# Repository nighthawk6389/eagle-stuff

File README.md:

# eagle-stuff
Stuff I made for PCB in Eagle

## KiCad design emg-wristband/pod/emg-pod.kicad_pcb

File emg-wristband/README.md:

# EMG wristband: main pod, rev A

KiCad project for the main pod: two ADS1298 converters, a Seeed XIAO nRF52840 Sense, a 3.0 V analog rail
with a USB interlock, and a vibration-motor driver. The brief is in `CLAUDE.md`. What is still
uncertain is in `OPEN.md`; read that before trusting anything here.

Status (2026-11-28): schematic drawn and ERC clean; board laid out and routed, 49 x 49 mm with a notch
under the antenna, four layers; reviewed once and reworked; fabrication files written, for the single
board and for the board in a 74 x 74 mm assembly frame; reviewed a second time, with findings still
open (`OPEN.md`, "Second review"). Nothing has been ordered or built. The layout's open points are under
"Layout" in `OPEN.md`.

## Where things are

| Path | What |
|---|---|
| `out/emg-pod-schematic.pdf` | The schematic for review, five pages |
| `out/bom-jlcpcb.csv` | Bill of materials from the schematic, JLCPCB columns, one LCSC number per line |
| `out/stock-check.md` | Stock and assembly type of every BOM line, with the date it was read |
| `out/erc.rpt` | KiCad's ERC report |
| `out/fab/` | The single board: Gerbers and drill files (also zipped), `cpl-jlcpcb.csv` (placement) and the BOM |
| `out/fab-panel/` | The same board in its 74 x 74 mm assembly frame: **the files for a JLCPCB Standard-assembly order** |
| `out/drc.rpt`, `out/drc-panel.rpt` | KiCad's DRC reports for the routed board and for the frame |
| `out/board-top.png`, `out/board-bottom.png`, `out/panel-top.png` | KiCad's rendering of the bare board, both sides, and of the frame |
| `pod/` | The KiCad 9 project (`emg-pod.kicad_pro`, schematic and `emg-pod.kicad_pcb`) and the frame (`emg-pod-panel.kicad_pcb`). Opens in KiCad 9 or newer |
| `pod/lib/` | Every symbol the schematic uses, and Seeed's XIAO footprint (plus a copy without the two NFC pads) |
| `gen/` | The Python that writes the schematic and the board |
| `tools/` | JLCPCB stock lookup |
| `docs/sources.md` | The datasheets and Seeed files each pin table came from |

## The schematic is generated

`gen/build.py` writes the `.kicad_sch` files. **Edits made in KiCad's schematic editor are lost the
next time it runs.** Either keep changing the generator, or stop using it and edit in KiCad from then on.

    python3 gen/build.py           # needs KiCad 9's kicad-cli on the path
    python3 tools/stock_report.py  # re-reads stock from jlcpcb.com

`build.py` does four things: writes the sheets, runs ERC, exports KiCad's netlist and compares all 552
pins with the tables in `gen/design.py` (which take their pin numbers from `gen/parts.py`, copied from
the datasheets), and exports the PDF and BOM. It exits non-zero if ERC or the comparison fails.

- `gen/parts.py`: pin tables and LCSC numbers. Each table names its datasheet.
- `gen/design.py`: which pin goes to which net, and where each part is drawn. The board is built from
  the same tables, so schematic and board cannot disagree about a net.
- `gen/kisch.py`, `gen/sexp.py`: KiCad file writing.

## The board is generated too

Five steps, each a script. **Edits made in KiCad's board editor are lost when they run again**, same
as for the schematic.

    /usr/bin/python3 gen/board.py                      # placement, rules, fixed routes -> pod/emg-pod-unrouted.kicad_pcb
    /usr/bin/python3 gen/route.py freerouting-2.1.0.jar   # autoroute the rest (Freerouting, about 9 minutes)
    /usr/bin/python3 gen/finish.py                     # leftovers, ground pours, plane vias, silkscreen -> pod/emg-pod.kicad_pcb
    /usr/bin/python3 gen/fab.py                        # Gerbers, drill, placement file -> out/fab/
    /usr/bin/python3 gen/panel.py                      # the board in its assembly frame -> pod/emg-pod-panel.kicad_pcb, out/fab-panel/

They need the `pcbnew` Python module that comes with KiCad 9 (the system Python on Ubuntu) and, for
`route.py`, Java and the Freerouting 2.1.0 jar from github.com/freerouting/freerouting (not in this repo).

- `gen/board.py` holds everything that was decided by hand: the outline, the design rules, where each
  part sits, and the routes that must not be left to an autorouter. Those are the 32 electrode lines
  (connector, resistor array, converter pin, in one straight line on the top layer), their fan-out on
  the back to the filter capacitors and to the ESD arrays, the via to a plane for every supply and
  ground pin of the converters, VCAP1, a ground via beside every ground pad, and lanes on the back for
  the seven nets that cross from the XIAO to the left half below the notch (five signals, the battery
  and VBUS; a lane the routers end up not using is removed again). The outline, with its
  notch under the XIAO's antenna, and the keep-outs under the module's bare pads are there too. It also names the
  areas reserved for the input lines (`quiet_zones`): the fan-out on the back around each converter
  and the stubs under it on the front. The routers lay nothing there.
- `gen/route.py` hands the rest to Freerouting. Ground is left out of that: ground pads are joined by
  the plane, the pours on both outer layers and the vias `finish.py` adds.
- `gen/finish.py` completes what Freerouting gave up on with a small grid router (`gen/lastmile.py`),
  pours ground on the outer layers, gives supply pads a via to their plane, stitches the pours to the
  ground plane, removes dead-end stubs, and runs KiCad's DRC. It prints what is still open, if anything.
- `gen/fab.py` writes the Gerbers, drill files and placement file, checks every pad's net against
  `gen/design.py`, checks that no routed track entered a reserved area and that the planes are
  filled between the vias of each row, reports how close other signals come to an input line and
  how close vias come to pads, and writes the full DRC report. It exits non-zero unless DRC has no
  errors, nothing is unconnected, the reserved areas are clean and the planes have no gaps.

- `gen/panel.py` copies the finished board into a 74 x 74 mm frame (JLCPCB's smallest size for
  Standard assembly is 70 x 70): a routed slot around the board, five tabs with a row of small holes each,
  three fiducials and four tooling holes on the rails. It does not move the board or refill its
  zones, checks that all copper is the same as in the single board, and runs DRC on the result.
  Run it again whenever `pod/emg-pod.kicad_pcb` changes. How to order and what is unverified:
  `OPEN.md`.

Any change to `gen/board.py` moves many of the autorouted tracks on the next run. The board in `pod/`
is the result of one run, and `out/fab/` and `out/fab-panel/` were made from exactly that file.

Layers: 1 signal and parts, 2 ground (one plane, no splits), 3 supplies (DVDD above y = 26.0 mm, AVDD
below, ground
fill elsewhere), 4 signal. No parts on the back; five bare pads are there, under the XIAO (SWD, ground and 3.3 V for a probe).

## Sheets

1. Overview: rails and the XIAO pin map.
2. Power: battery connector, LP5907 3.0 V analog rail, the USB interlock, the motor driver.
3. MCU: the XIAO and its test points, including SWD.
4. Converter A: strip connector, ESD arrays, input network, ADS1298, bypass, bias drive, clock master.
5. Converter B: the same block, clocked from A, bias amplifier unused.

Converter A parts are numbered 100-199 and converter B parts 200-299, so each block stays
recognisable when the pod is split later.

## Choices made while drawing (details in OPEN.md)

- **XIAO Sense on Standard assembly** (owner's decision). JLCPCB marks the Sense "Standard Only"; every
  other part is cleared for Economic. Standard assembly wants boards of at least 70 x 70 mm with rails and fiducials, hence the frame.
- **47k in every skin-facing line**, so any path through the wearer crosses 94k.
- **Digital supply always on, analog supply gated.** The interlock only switches the 3.0 V rail.
- **Interlock:** a MOSFET holds the regulator's enable low whenever the XIAO's 5V pin (USB VBUS) is up.
- **SPI clock and data-in on D5 and D4**, the only XIAO pins Nordic rates for fast signals.
- **Motor on two wire pads**, with a series resistor sized for a 3 V coin motor on a 4.2 V cell.
- **Tantalum on VCAP1**, because the datasheet warns about ceramics there on boards that vibrate.

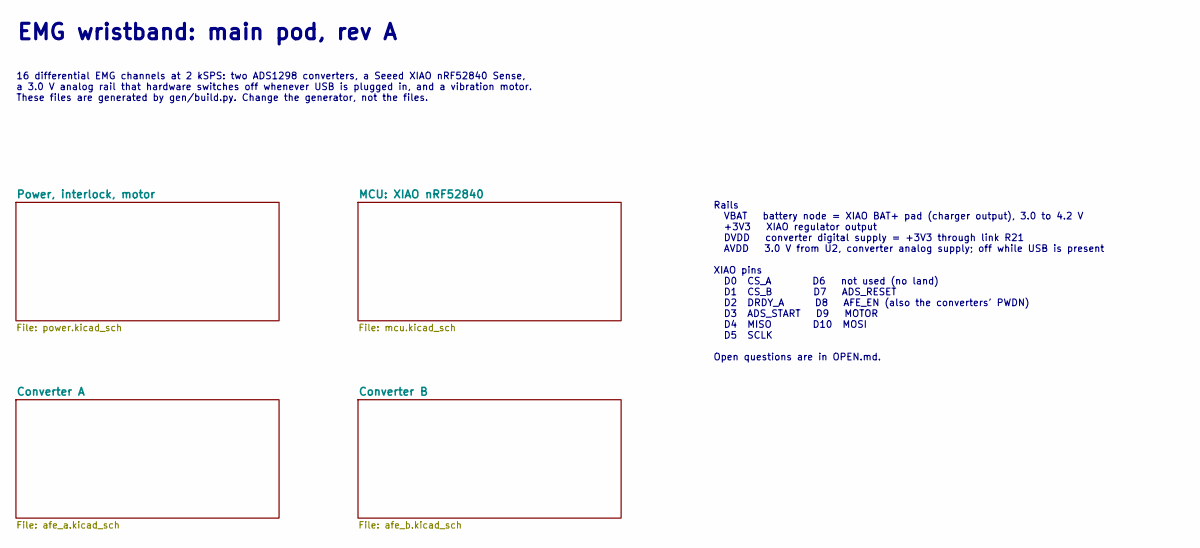
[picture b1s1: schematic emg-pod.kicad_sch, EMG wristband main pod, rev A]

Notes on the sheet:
EMG wristband: main pod, rev A
16 differential EMG channels at 2 kSPS: two ADS1298 converters, a Seeed XIAO nRF52840 Sense, a 3.0 V analog rail that hardware switches off whenever USB is plugged in, and a vibration motor. These files are generated by gen/build.py. Change the generator, not the files.
Rails VBAT battery node = XIAO BAT+ pad (charger output), 3.0 to 4.2 V +3V3 XIAO regulator output DVDD converter digital supply = +3V3 through link R21 AVDD 3.0 V from U2, converter analog supply; off while USB is present XIAO pins D0 CS_A D6 not used (no land) D1 CS_B D7 ADS_RESET D2 DRDY_A D8 AFE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

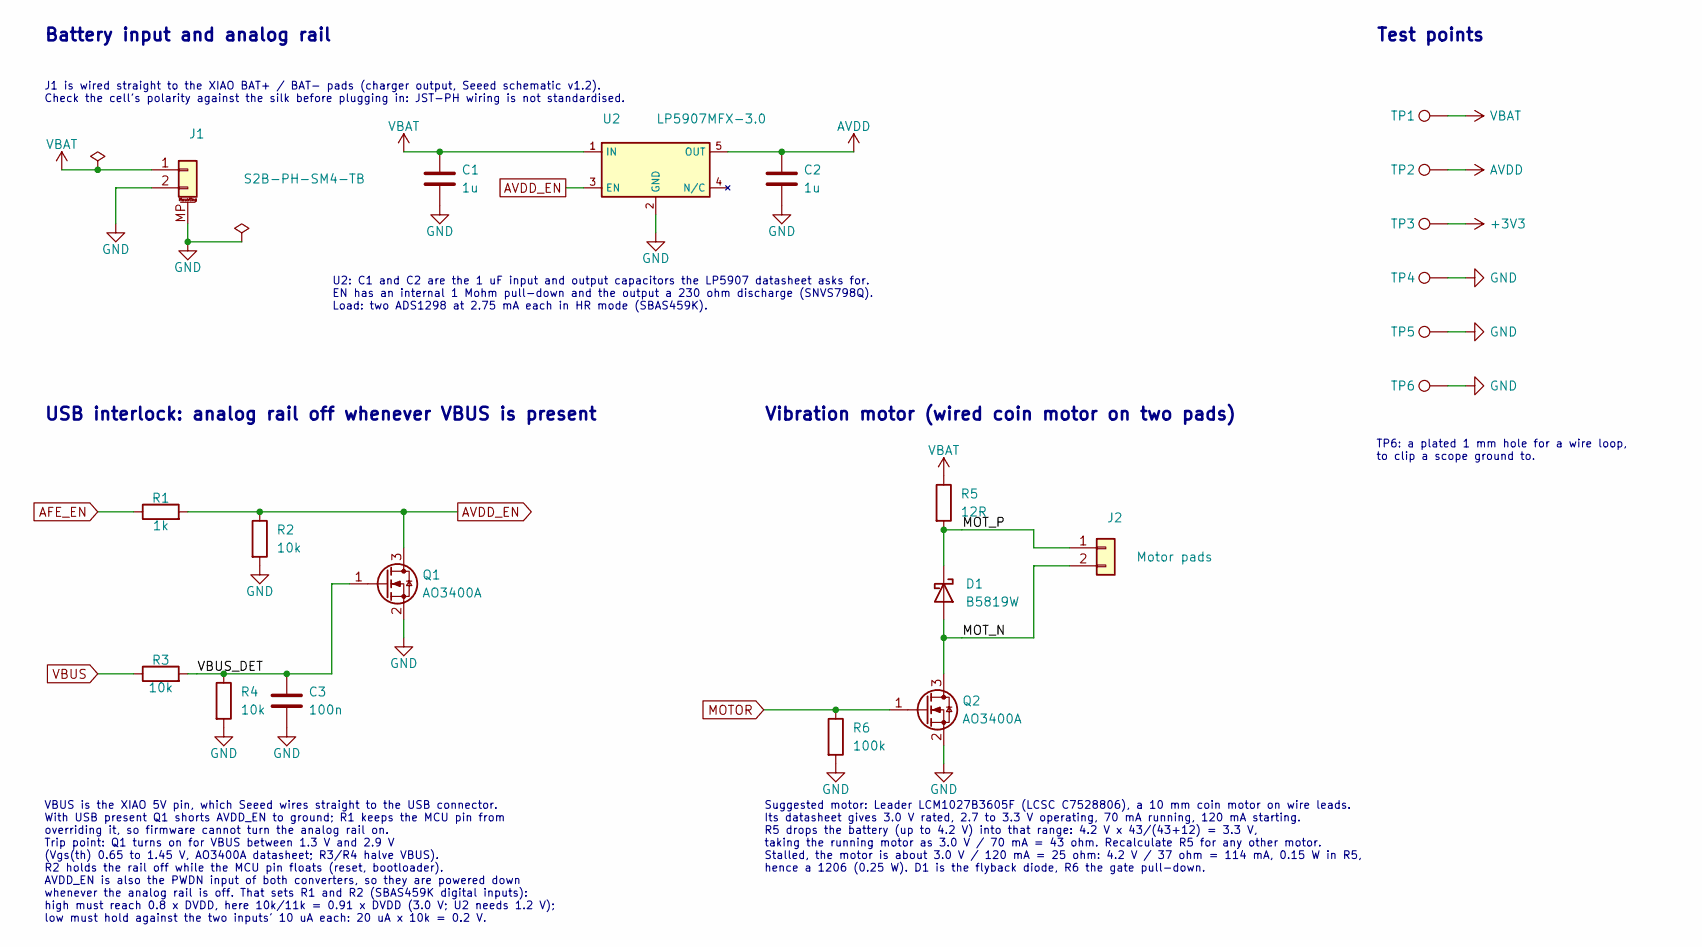
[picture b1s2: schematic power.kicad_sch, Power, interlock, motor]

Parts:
C1, C2: 1u; C_0402_1005Metric; MPN CL05A105KA5NQNC; LCSC C52923
C3: 100n; C_0402_1005Metric; MPN CL05B104KO5NNNC; LCSC C1525
D1: B5819W; D_SOD-123; MPN B5819W SL; LCSC C8598
J1: S2B-PH-SM4-TB; JST_PH_S2B-PH-SM4-TB_1x02-1MP_P2.00mm_Horizontal; MPN S2B-PH-SM4-TB(LF)(SN); LCSC C295747
J2: Motor pads; SolderWire-0.127sqmm_1x02_P3.7mm_D0.48mm_OD1mm
Q1, Q2: AO3400A; SOT-23; MPN AO3400A; LCSC C20917
R1: 1k; R_0402_1005Metric; MPN 0402WGF1001TCE; LCSC C11702
R2, R3, R4: 10k; R_0402_1005Metric; MPN 0402WGF1002TCE; LCSC C25744
R5: 12R; R_1206_3216Metric; MPN 1206W4F120JT5E; LCSC C17913
R6: 100k; R_0402_1005Metric; MPN 0402WGF1003TCE; LCSC C25741
TP1, TP2, TP3, TP4, TP5: TestPoint; TestPoint_Pad_D1.0mm_bare
TP6: TestPoint; TestPoint_THTPad_D2.0mm_Drill1.0mm
U2: LP5907MFX-3.0; SOT-23-5; MPN LP5907MFX-3.0/NOPB; LCSC C475492

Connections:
+3V3: TP3.1; also elsewhere on the board
AFE_EN: R1.1; also elsewhere on the board
AVDD: C2.1, TP2.1, U2.5 (OUT); also elsewhere on the board
AVDD_EN: Q1.3 (D), R1.2, R2.1, U2.3 (EN); also elsewhere on the board
GND: C1.2, C2.2, C3.2, J1.2, J1.MP (MountPin), Q1.2 (S), Q2.2 (S), R2.2, R4.2, R6.2, TP4.1, TP5.1, TP6.1, U2.2 (GND); also elsewhere on the board
MOTOR: Q2.1 (G), R6.1; also elsewhere on the board
MOT_N: D1.2 (A), J2.2, Q2.3 (D)
MOT_P: D1.1 (K), J2.1, R5.2
VBAT: C1.1, J1.1, R5.1, TP1.1, U2.1 (IN); also elsewhere on the board
VBUS: R3.1; also elsewhere on the board
VBUS_DET: C3.1, Q1.1 (G), R3.2, R4.1

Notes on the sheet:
Battery input and analog rail
J1 is wired straight to the XIAO BAT+ / BAT- pads (charger output, Seeed schematic v1.2). Check the cell's polarity against the silk before plugging in: JST-PH wiring is not standardised.
U2: C1 and C2 are the 1 uF input and output capacitors the LP5907 datasheet asks for. EN has an internal 1 Mohm pull-down and the output a 230 ohm discharge (SNVS798Q). Load: two ADS1298 at 2.75 mA each in HR mode (SBAS459K).
USB interlock: analog rail off whenever VBUS is present
VBUS is the XIAO 5V pin, which Seeed wires straight to the USB connector. With USB present Q1 shorts AVDD_EN to ground; R1 keeps the MCU pin from overriding it, so firmware cannot turn the analog rail on. Trip point: Q1 turns on for VBUS between 1.3 V and 2.9 V (Vgs(th) 0.65 to 1.45 V, AO3400A data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
Vibration motor (wired coin motor on two pads)
Suggested motor: Leader LCM1027B3605F (LCSC C7528806), a 10 mm coin motor on wire leads. Its datasheet gives 3.0 V rated, 2.7 to 3.3 V operating, 70 mA running, 120 mA starting. R5 drops the battery (up to 4.2 V) into that range: 4.2 V x 43/(43+12) = 3.3 V, taking the running motor as 3.0 V / 70 mA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
Test points
TP6: a plated 1 mm hole for a wire loop, to clip a scope ground to.

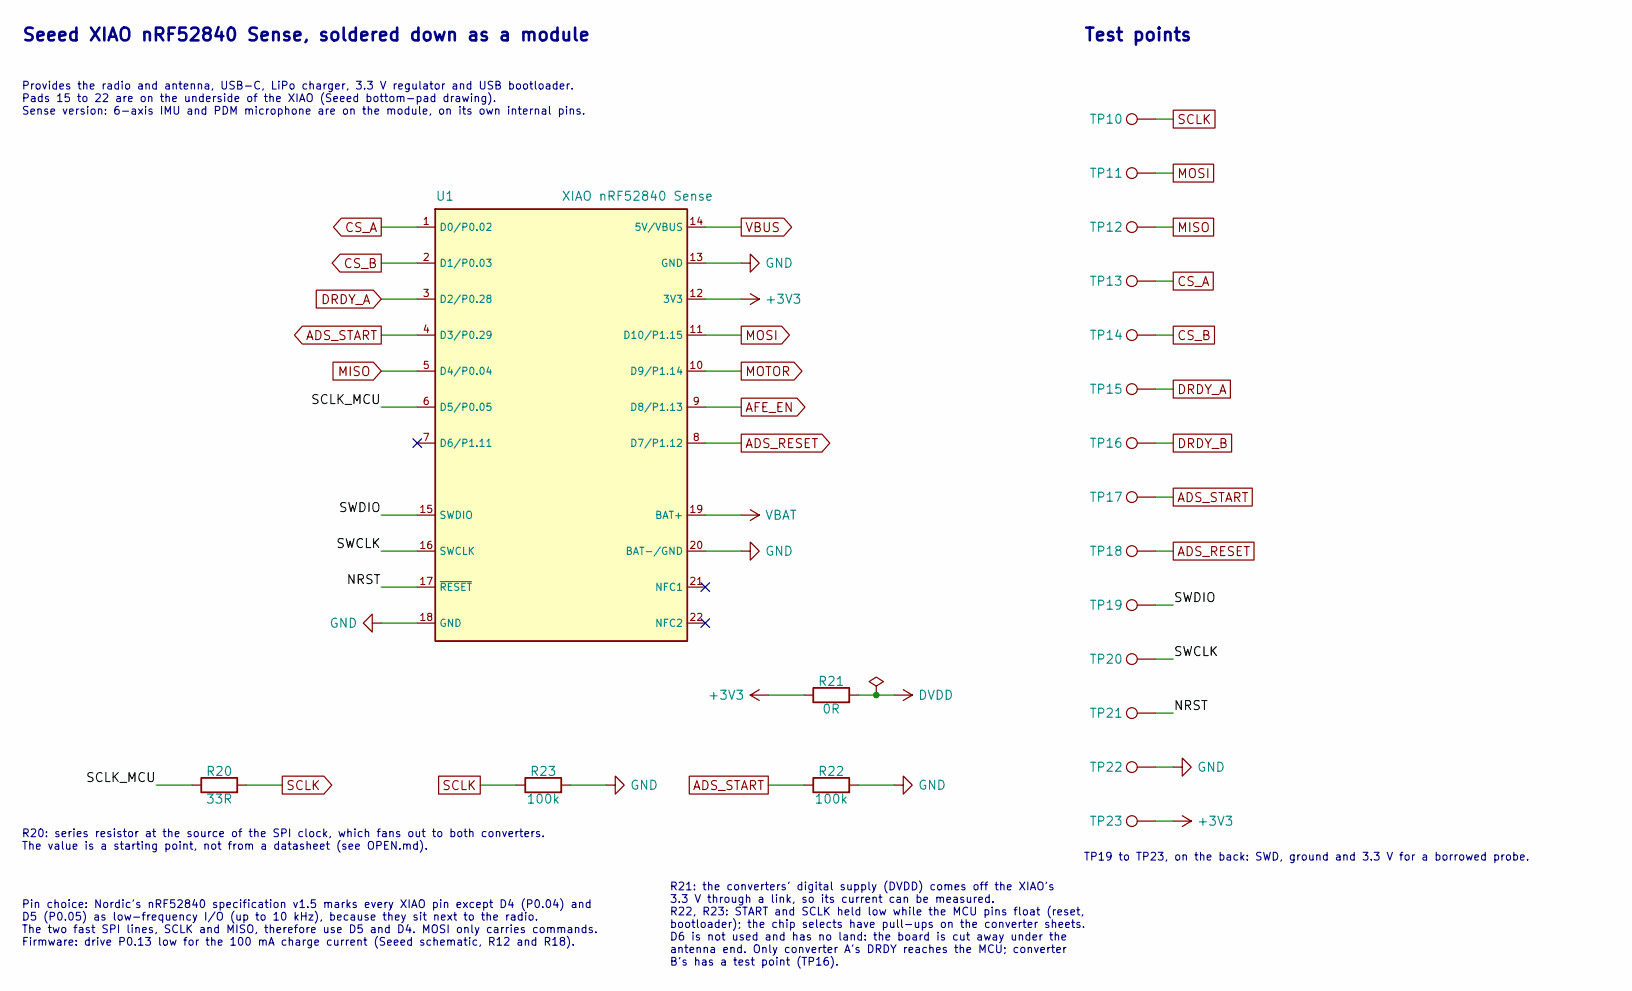
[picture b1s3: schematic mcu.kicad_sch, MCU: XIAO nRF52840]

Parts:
R20: 33R; R_0402_1005Metric; MPN 0402WGF330JTCE; LCSC C25105
R21: 0R; R_0402_1005Metric; MPN 0402WGF0000TCE; LCSC C17168
R22, R23: 100k; R_0402_1005Metric; MPN 0402WGF1003TCE; LCSC C25741
TP10, TP11, TP12, TP13, TP14, TP15, TP16, TP17, TP18, TP19, TP20, TP21, TP22, TP23: TestPoint; TestPoint_Pad_D1.0mm_bare
U1: XIAO nRF52840 Sense; XIAO-nRF52840-SMD-pod; MPN Seeed 102010469; LCSC C17401557

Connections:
+3V3: R21.1, TP23.1, U1.12 (3V3); also elsewhere on the board
ADS_RESET: TP18.1, U1.8 (D7/P1.12); also elsewhere on the board
ADS_START: R22.1, TP17.1, U1.4 (D3/P0.29); also elsewhere on the board
AFE_EN: U1.9 (D8/P1.13); also elsewhere on the board
CS_A: TP13.1, U1.1 (D0/P0.02); also elsewhere on the board
CS_B: TP14.1, U1.2 (D1/P0.03); also elsewhere on the board
DRDY_A: TP15.1, U1.3 (D2/P0.28); also elsewhere on the board
DRDY_B: TP16.1; also elsewhere on the board
DVDD: R21.2; also elsewhere on the board
GND: R22.2, R23.2, TP22.1, U1.13 (GND), U1.18 (GND), U1.20 (BAT-/GND); also elsewhere on the board
MISO: TP12.1, U1.5 (D4/P0.04); also elsewhere on the board
MOSI: TP11.1, U1.11 (D10/P1.15); also elsewhere on the board
MOTOR: U1.10 (D9/P1.14); also elsewhere on the board
NRST: TP21.1, U1.17 (~RESET)
SCLK: R20.2, R23.1, TP10.1; also elsewhere on the board
SCLK_MCU: R20.1, U1.6 (D5/P0.05)
SWCLK: TP20.1, U1.16 (SWCLK)
SWDIO: TP19.1, U1.15 (SWDIO)
VBAT: U1.19 (BAT+); also elsewhere on the board
VBUS: U1.14 (5V/VBUS); also elsewhere on the board

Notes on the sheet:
Seeed XIAO nRF52840 Sense, soldered down as a module
Provides the radio and antenna, USB-C, LiPo charger, 3.3 V regulator and USB bootloader. Pads 15 to 22 are on the underside of the XIAO (Seeed bottom-pad drawing). Sense version: 6-axis IMU and PDM microphone are on the module, on its own internal pins.
R20: series resistor at the source of the SPI clock, which fans out to both converters. The value is a starting point, not from a datasheet (see OPEN.md).
R21: the converters' digital supply (DVDD) comes off the XIAO's 3.3 V through a link, so its current can be measured. R22, R23: START and SCLK held low while the MCU pins float (reset, bootloader); the chip selects have pull-ups on the converter sheets. D6 is not used and has no land: the board is 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
Pin choice: Nordic's nRF52840 specification v1.5 marks every XIAO pin except D4 (P0.04) and D5 (P0.05) as low-frequency I/O (up to 10 kHz), because they sit next to the radio. The two fast SPI lines, SCLK and MISO, therefore use D5 and D4. MOSI only carries commands. Firmware: drive P0.13 low for t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
Test points
TP19 to TP23, on the back: SWD, ground and 3.3 V for a borrowed probe.

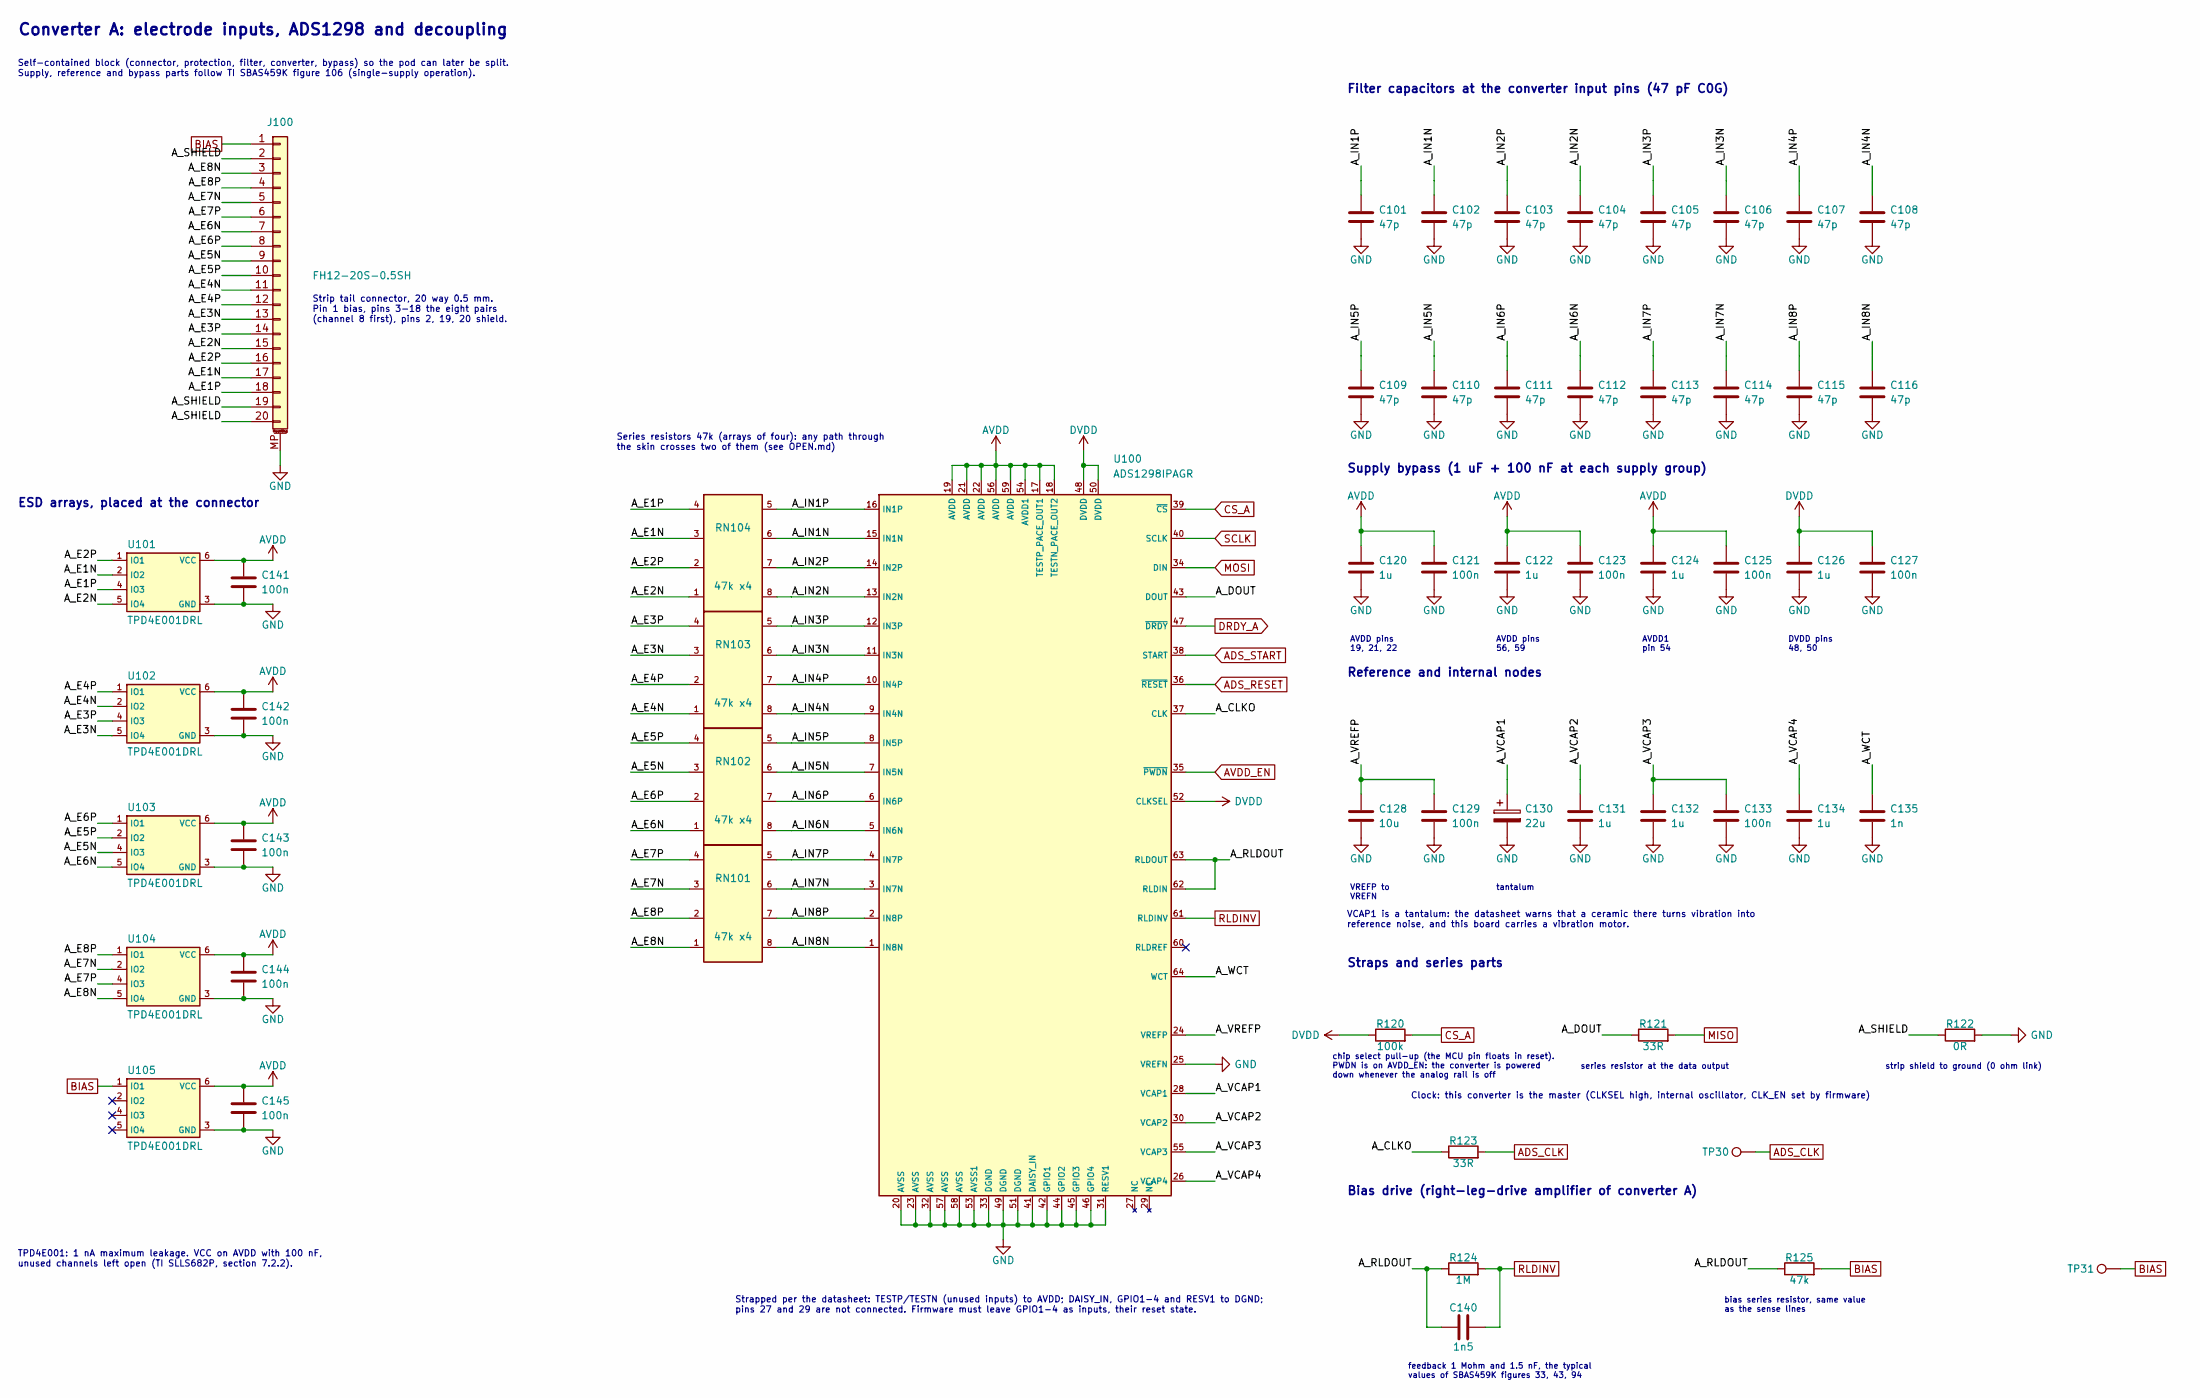
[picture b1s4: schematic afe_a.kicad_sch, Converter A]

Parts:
C101, C102, C103, C104, C105, C106, C107, C108, C109, C110, C111, C112, C113, C114, C115, C116: 47p; C_0402_1005Metric; MPN 0402CG470J500NT; LCSC C1567
C120, C122, C124, C126, C131, C132, C134: 1u; C_0402_1005Metric; MPN CL05A105KA5NQNC; LCSC C52923
C121, C123, C125, C127, C129, C133, C141, C142, C143, C144, C145: 100n; C_0402_1005Metric; MPN CL05B104KO5NNNC; LCSC C1525
C128: 10u; C_0603_1608Metric; MPN CL10A106KP8NNNC; LCSC C19702
C130: 22u; CP_EIA-3528-21_Kemet-B; MPN T491B226M010AT; LCSC C117031
C135: 1n; C_0402_1005Metric; MPN 0402B102K500NT; LCSC C1523
C140: 1n5; C_0603_1608Metric; MPN 0603B152K500NT; LCSC C1595
J100: FH12-20S-0.5SH; Hirose_FH12-20S-0.5SH_1x20-1MP_P0.50mm_Horizontal; MPN FH12-20S-0.5SH(55); LCSC C596730
R120: 100k; R_0402_1005Metric; MPN 0402WGF1003TCE; LCSC C25741
R121, R123: 33R; R_0402_1005Metric; MPN 0402WGF330JTCE; LCSC C25105
R122: 0R; R_0402_1005Metric; MPN 0402WGF0000TCE; LCSC C17168
R124: 1M; R_0402_1005Metric; MPN 0402WGF1004TCE; LCSC C26083
R125: 47k; R_0402_1005Metric; MPN 0402WGF4702TCE; LCSC C25792
RN101, RN102, RN103, RN104: 47k x4; R_Array_Convex_4x0402; MPN 4D02WGJ0473TCE; LCSC C2028
TP30, TP31: TestPoint; TestPoint_Pad_D1.0mm_bare
U100: ADS1298IPAGR; TQFP-64_10x10mm_P0.5mm; MPN ADS1298IPAGR; LCSC C527440
U101, U102, U103, U104, U105: TPD4E001DRL; SOT-563; MPN TPD4E001DRLR; LCSC C527516

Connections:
ADS_CLK: R123.2, TP30.1; also elsewhere on the board
ADS_RESET: U100.36 (~RESET); also elsewhere on the board
ADS_START: U100.38 (START); also elsewhere on the board
AVDD: C120.1, C121.1, C122.1, C123.1, C124.1, C125.1, C141.1, C142.1, C143.1, C144.1, C145.1, U100.17 (TESTP_PACE_OUT1), U100.18 (TESTN_PACE_OUT2), U100.19 (AVDD), U100.21 (AVDD), U100.22 (AVDD), U100.54 (AVDD1), U100.56 (AVDD), U100.59 (AVDD), U101.6 (VCC), U102.6 (VCC), U103.6 (VCC), U104.6 (VCC), U105.6 (VCC); also elsewhere on the board
AVDD_EN: U100.35 (~PWDN); also elsewhere on the board
A_CLKO: R123.1, U100.37 (CLK)
A_DOUT: R121.1, U100.43 (DOUT)
A_E1N: J100.17, RN104.3, U101.2 (IO2)
A_E1P: J100.18, RN104.4, U101.4 (IO3)
A_E2N: J100.15, RN104.1, U101.5 (IO4)
A_E2P: J100.16, RN104.2, U101.1 (IO1)
A_E3N: J100.13, RN103.3, U102.5 (IO4)
A_E3P: J100.14, RN103.4, U102.4 (IO3)
A_E4N: J100.11, RN103.1, U102.2 (IO2)
A_E4P: J100.12, RN103.2, U102.1 (IO1)
A_E5N: J100.9, RN102.3, U103.4 (IO3)
A_E5P: J100.10, RN102.4, U103.2 (IO2)
A_E6N: J100.7, RN102.1, U103.5 (IO4)
A_E6P: J100.8, RN102.2, U103.1 (IO1)
A_E7N: J100.5, RN101.3, U104.2 (IO2)
A_E7P: J100.6, RN101.4, U104.4 (IO3)
A_E8N: J100.3, RN101.1, U104.5 (IO4)
A_E8P: J100.4, RN101.2, U104.1 (IO1)
A_IN1N: C102.1, RN104.6, U100.15 (IN1N)
A_IN1P: C101.1, RN104.5, U100.16 (IN1P)
A_IN2N: C104.1, RN104.8, U100.13 (IN2N)
A_IN2P: C103.1, RN104.7, U100.14 (IN2P)
A_IN3N: C106.1, RN103.6, U100.11 (IN3N)
A_IN3P: C105.1, RN103.5, U100.12 (IN3P)
A_IN4N: C108.1, RN103.8, U100.9 (IN4N)
A_IN4P: C107.1, RN103.7, U100.10 (IN4P)
A_IN5N: C110.1, RN102.6, U100.7 (IN5N)
A_IN5P: C109.1, RN102.5, U100.8 (IN5P)
A_IN6N: C112.1, RN102.8, U100.5 (IN6N)
A_IN6P: C111.1, RN102.7, U100.6 (IN6P)
A_IN7N: C114.1, RN101.6, U100.3 (IN7N)
A_IN7P: C113.1, RN101.5, U100.4 (IN7P)
A_IN8N: C116.1, RN101.8, U100.1 (IN8N)
A_IN8P: C115.1, RN101.7, U100.2 (IN8P)
A_RLDOUT: C140.1, R124.1, R125.1, U100.62 (RLDIN), U100.63 (RLDOUT)
A_SHIELD: J100.2, J100.19, J100.20, R122.1
A_VCAP1: C130.1, U100.28 (VCAP1)
A_VCAP2: C131.1, U100.30 (VCAP2)
A_VCAP3: C132.1, C133.1, U100.55 (VCAP3)
A_VCAP4: C134.1, U100.26 (VCAP4)
A_VREFP: C128.1, C129.1, U100.24 (VREFP)
A_WCT: C135.1, U100.64 (WCT)
BIAS: J100.1, R125.2, TP31.1, U105.1 (IO1); also elsewhere on the board
CS_A: R120.2, U100.39 (~CS); also elsewhere on the board
DRDY_A: U100.47 (~DRDY); also elsewhere on the board
DVDD: C126.1, C127.1, R120.1, U100.48 (DVDD), U100.50 (DVDD), U100.52 (CLKSEL); also elsewhere on the board
GND: C101.2, C102.2, C103.2, C104.2, C105.2, C106.2, C107.2, C108.2, C109.2, C110.2, C111.2, C112.2, C113.2, C114.2, C115.2, C116.2, C120.2, C121.2, C122.2, C123.2, C124.2, C125.2, C126.2, C127.2, C128.2, C129.2, C130.2, C131.2, C132.2, C133.2, C134.2, C135.2, C141.2, C142.2, C143.2, C144.2, C145.2, J100.MP (MountPin), R122.2, U100.20 (AVSS), U100.23 (AVSS), U100.25 (VREFN), U100.31 (RESV1), U100.32 (AVSS), U100.33 (DGND), U100.41 (DAISY_IN), U100.42 (GPIO1), U100.44 (GPIO2), U100.45 (GPIO3), U100.46 (GPIO4), U100.49 (DGND), U100.51 (DGND), U100.53 (AVSS1), U100.57 (AVSS), U100.58 (AVSS), U101.3 (GND), U102.3 (GND), U103.3 (GND), U104.3 (GND), U105.3 (GND); also elsewhere on the board
MISO: R121.2; also elsewhere on the board
MOSI: U100.34 (DIN); also elsewhere on the board
RLDINV: C140.2, R124.2, U100.61 (RLDINV); also elsewhere on the board
SCLK: U100.40 (SCLK); also elsewhere on the board

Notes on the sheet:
Converter A: electrode inputs, ADS1298 and decoupling
Self-contained block (connector, protection, filter, converter, bypass) so the pod can later be split. Supply, reference and bypass parts follow TI SBAS459K figure 106 (single-supply operation).
Strip tail connector, 20 way 0.5 mm. Pin 1 bias, pins 3-18 the eight pairs (channel 8 first), pins 2, 19, 20 shield.
ESD arrays, placed at the connector
TPD4E001: 1 nA maximum leakage. VCC on AVDD with 100 nF, unused channels left open (TI SLLS682P, section 7.2.2).
Strapped per the datasheet: TESTP/TESTN (unused inputs) to AVDD; DAISY_IN, GPIO1-4 and RESV1 to DGND; pins 27 and 29 are not connected. Firmware must leave GPIO1-4 as inputs, their reset state.
Series resistors 47k (arrays of four): any path through the skin crosses two of them (see OPEN.md)
Filter capacitors at the converter input pins (47 pF C0G)
Supply bypass (1 uF + 100 nF at each supply group)
AVDD pins 19, 21, 22
AVDD pins 56, 59
AVDD1 pin 54
DVDD pins 48, 50
Reference and internal nodes
VREFP to VREFN
tantalum
VCAP1 is a tantalum: the datasheet warns that a ceramic there turns vibration into reference noise, and this board carries a vibration motor.
Straps and series parts
chip select pull-up (the MCU pin floats in reset). PWDN is on AVDD_EN: the converter is powered down whenever the analog rail is off
series resistor at the data output
strip shield to ground (0 ohm link)
Clock: this converter is the master (CLKSEL high, internal oscillator, CLK_EN set by firmware)
Bias drive (right-leg-drive amplifier of converter A)
feedback 1 Mohm and 1.5 nF, the typical values of SBAS459K figures 33, 43, 94
bias series resistor, same value as the sense lines

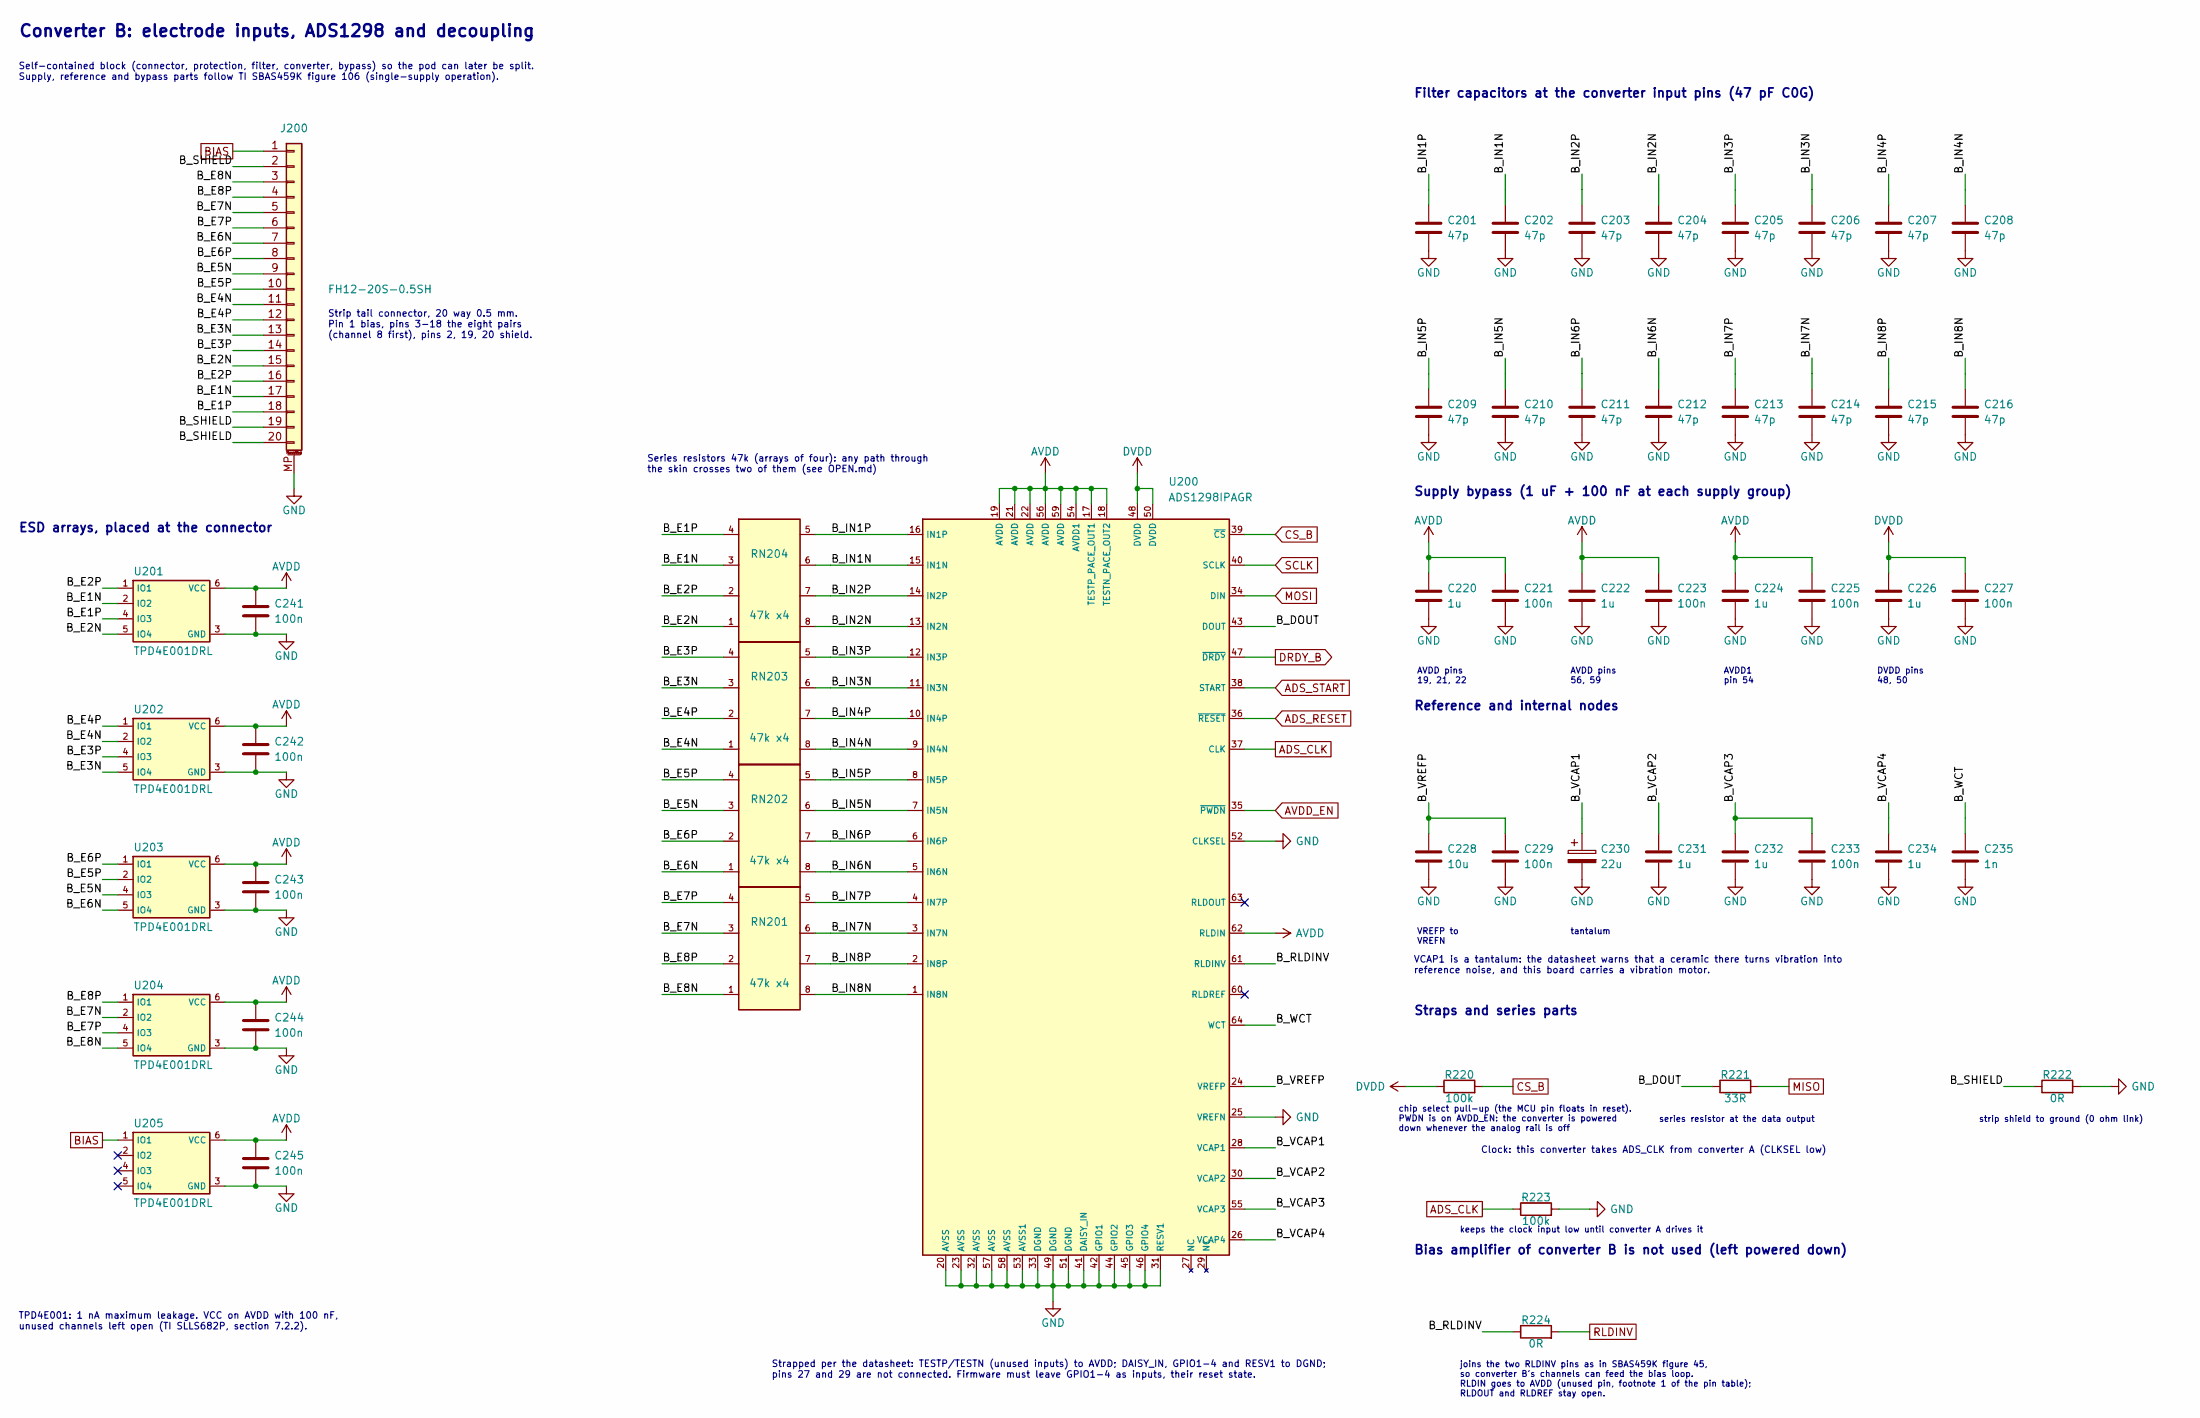
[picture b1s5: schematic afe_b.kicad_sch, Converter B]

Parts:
C201, C202, C203, C204, C205, C206, C207, C208, C209, C210, C211, C212, C213, C214, C215, C216: 47p; C_0402_1005Metric; MPN 0402CG470J500NT; LCSC C1567
C220, C222, C224, C226, C231, C232, C234: 1u; C_0402_1005Metric; MPN CL05A105KA5NQNC; LCSC C52923
C221, C223, C225, C227, C229, C233, C241, C242, C243, C244, C245: 100n; C_0402_1005Metric; MPN CL05B104KO5NNNC; LCSC C1525
C228: 10u; C_0603_1608Metric; MPN CL10A106KP8NNNC; LCSC C19702
C230: 22u; CP_EIA-3528-21_Kemet-B; MPN T491B226M010AT; LCSC C117031
C235: 1n; C_0402_1005Metric; MPN 0402B102K500NT; LCSC C1523
J200: FH12-20S-0.5SH; Hirose_FH12-20S-0.5SH_1x20-1MP_P0.50mm_Horizontal; MPN FH12-20S-0.5SH(55); LCSC C596730
R220, R223: 100k; R_0402_1005Metric; MPN 0402WGF1003TCE; LCSC C25741
R221: 33R; R_0402_1005Metric; MPN 0402WGF330JTCE; LCSC C25105
R222, R224: 0R; R_0402_1005Metric; MPN 0402WGF0000TCE; LCSC C17168
RN201, RN202, RN203, RN204: 47k x4; R_Array_Convex_4x0402; MPN 4D02WGJ0473TCE; LCSC C2028
U200: ADS1298IPAGR; TQFP-64_10x10mm_P0.5mm; MPN ADS1298IPAGR; LCSC C527440
U201, U202, U203, U204, U205: TPD4E001DRL; SOT-563; MPN TPD4E001DRLR; LCSC C527516

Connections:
ADS_CLK: R223.1, U200.37 (CLK); also elsewhere on the board
ADS_RESET: U200.36 (~RESET); also elsewhere on the board
ADS_START: U200.38 (START); also elsewhere on the board
AVDD: C220.1, C221.1, C222.1, C223.1, C224.1, C225.1, C241.1, C242.1, C243.1, C244.1, C245.1, U200.17 (TESTP_PACE_OUT1), U200.18 (TESTN_PACE_OUT2), U200.19 (AVDD), U200.21 (AVDD), U200.22 (AVDD), U200.54 (AVDD1), U200.56 (AVDD), U200.59 (AVDD), U200.62 (RLDIN), U201.6 (VCC), U202.6 (VCC), U203.6 (VCC), U204.6 (VCC), U205.6 (VCC); also elsewhere on the board
AVDD_EN: U200.35 (~PWDN); also elsewhere on the board
BIAS: J200.1, U205.1 (IO1); also elsewhere on the board
B_DOUT: R221.1, U200.43 (DOUT)
B_E1N: J200.17, RN204.3, U201.2 (IO2)
B_E1P: J200.18, RN204.4, U201.4 (IO3)
B_E2N: J200.15, RN204.1, U201.5 (IO4)
B_E2P: J200.16, RN204.2, U201.1 (IO1)
B_E3N: J200.13, RN203.3, U202.5 (IO4)
B_E3P: J200.14, RN203.4, U202.4 (IO3)
B_E4N: J200.11, RN203.1, U202.2 (IO2)
B_E4P: J200.12, RN203.2, U202.1 (IO1)
B_E5N: J200.9, RN202.3, U203.4 (IO3)
B_E5P: J200.10, RN202.4, U203.2 (IO2)
B_E6N: J200.7, RN202.1, U203.5 (IO4)
B_E6P: J200.8, RN202.2, U203.1 (IO1)
B_E7N: J200.5, RN201.3, U204.2 (IO2)
B_E7P: J200.6, RN201.4, U204.4 (IO3)
B_E8N: J200.3, RN201.1, U204.5 (IO4)
B_E8P: J200.4, RN201.2, U204.1 (IO1)
B_IN1N: C202.1, RN204.6, U200.15 (IN1N)
B_IN1P: C201.1, RN204.5, U200.16 (IN1P)
B_IN2N: C204.1, RN204.8, U200.13 (IN2N)
B_IN2P: C203.1, RN204.7, U200.14 (IN2P)
B_IN3N: C206.1, RN203.6, U200.11 (IN3N)
B_IN3P: C205.1, RN203.5, U200.12 (IN3P)
B_IN4N: C208.1, RN203.8, U200.9 (IN4N)
B_IN4P: C207.1, RN203.7, U200.10 (IN4P)
B_IN5N: C210.1, RN202.6, U200.7 (IN5N)
B_IN5P: C209.1, RN202.5, U200.8 (IN5P)
B_IN6N: C212.1, RN202.8, U200.5 (IN6N)
B_IN6P: C211.1, RN202.7, U200.6 (IN6P)
B_IN7N: C214.1, RN201.6, U200.3 (IN7N)
B_IN7P: C213.1, RN201.5, U200.4 (IN7P)
B_IN8N: C216.1, RN201.8, U200.1 (IN8N)
B_IN8P: C215.1, RN201.7, U200.2 (IN8P)
B_RLDINV: R224.1, U200.61 (RLDINV)
B_SHIELD: J200.2, J200.19, J200.20, R222.1
B_VCAP1: C230.1, U200.28 (VCAP1)
B_VCAP2: C231.1, U200.30 (VCAP2)
B_VCAP3: C232.1, C233.1, U200.55 (VCAP3)
B_VCAP4: C234.1, U200.26 (VCAP4)
B_VREFP: C228.1, C229.1, U200.24 (VREFP)
B_WCT: C235.1, U200.64 (WCT)
CS_B: R220.2, U200.39 (~CS); also elsewhere on the board
DRDY_B: U200.47 (~DRDY); also elsewhere on the board
DVDD: C226.1, C227.1, R220.1, U200.48 (DVDD), U200.50 (DVDD); also elsewhere on the board
GND: C201.2, C202.2, C203.2, C204.2, C205.2, C206.2, C207.2, C208.2, C209.2, C210.2, C211.2, C212.2, C213.2, C214.2, C215.2, C216.2, C220.2, C221.2, C222.2, C223.2, C224.2, C225.2, C226.2, C227.2, C228.2, C229.2, C230.2, C231.2, C232.2, C233.2, C234.2, C235.2, C241.2, C242.2, C243.2, C244.2, C245.2, J200.MP (MountPin), R222.2, R223.2, U200.20 (AVSS), U200.23 (AVSS), U200.25 (VREFN), U200.31 (RESV1), U200.32 (AVSS), U200.33 (DGND), U200.41 (DAISY_IN), U200.42 (GPIO1), U200.44 (GPIO2), U200.45 (GPIO3), U200.46 (GPIO4), U200.49 (DGND), U200.51 (DGND), U200.52 (CLKSEL), U200.53 (AVSS1), U200.57 (AVSS), U200.58 (AVSS), U201.3 (GND), U202.3 (GND), U203.3 (GND), U204.3 (GND), U205.3 (GND); also elsewhere on the board
MISO: R221.2; also elsewhere on the board
MOSI: U200.34 (DIN); also elsewhere on the board
RLDINV: R224.2; also elsewhere on the board
SCLK: U200.40 (SCLK); also elsewhere on the board

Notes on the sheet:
Converter B: electrode inputs, ADS1298 and decoupling
Self-contained block (connector, protection, filter, converter, bypass) so the pod can later be split. Supply, reference and bypass parts follow TI SBAS459K figure 106 (single-supply operation).
Strip tail connector, 20 way 0.5 mm. Pin 1 bias, pins 3-18 the eight pairs (channel 8 first), pins 2, 19, 20 shield.
ESD arrays, placed at the connector
TPD4E001: 1 nA maximum leakage. VCC on AVDD with 100 nF, unused channels left open (TI SLLS682P, section 7.2.2).
Strapped per the datasheet: TESTP/TESTN (unused inputs) to AVDD; DAISY_IN, GPIO1-4 and RESV1 to DGND; pins 27 and 29 are not connected. Firmware must leave GPIO1-4 as inputs, their reset state.
Series resistors 47k (arrays of four): any path through the skin crosses two of them (see OPEN.md)
Filter capacitors at the converter input pins (47 pF C0G)
Supply bypass (1 uF + 100 nF at each supply group)
AVDD pins 19, 21, 22
AVDD pins 56, 59
AVDD1 pin 54
DVDD pins 48, 50
Reference and internal nodes
VREFP to VREFN
tantalum
VCAP1 is a tantalum: the datasheet warns that a ceramic there turns vibration into reference noise, and this board carries a vibration motor.
Straps and series parts
chip select pull-up (the MCU pin floats in reset). PWDN is on AVDD_EN: the converter is powered down whenever the analog rail is off
series resistor at the data output
strip shield to ground (0 ohm link)
Clock: this converter takes ADS_CLK from converter A (CLKSEL low)
keeps the clock input low until converter A drives it
Bias amplifier of converter B is not used (left powered down)
joins the two RLDINV pins as in SBAS459K figure 45, so converter B's channels can feed the bias loop. RLDIN goes to AVDD (unused pin, footnote 1 of the pin table); RLDOUT and RLDREF stay open.
